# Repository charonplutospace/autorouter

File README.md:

# autorouter
A test for an reinforement based autorouter
A test for an reinforement based autorouter

The readme describtion continues.

pip install -r requirements.txt
PyQt6

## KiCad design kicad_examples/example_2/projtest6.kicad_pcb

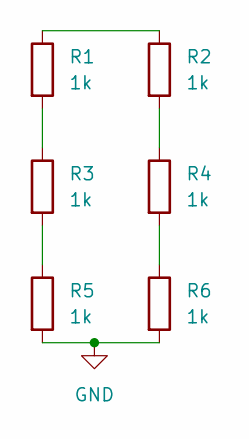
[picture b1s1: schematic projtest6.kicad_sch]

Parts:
R1, R2, R3, R4, R5, R6: 1k; R_1206_3216Metric

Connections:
GND: R5.2, R6.2
unnamed: R1.1, R2.1
unnamed: R1.2, R3.1
unnamed: R2.2, R4.1
unnamed: R3.2, R5.1
unnamed: R4.2, R6.1

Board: 2 copper layers, 6 parts (0 on the bottom side), 6 nets, no tracks yet.

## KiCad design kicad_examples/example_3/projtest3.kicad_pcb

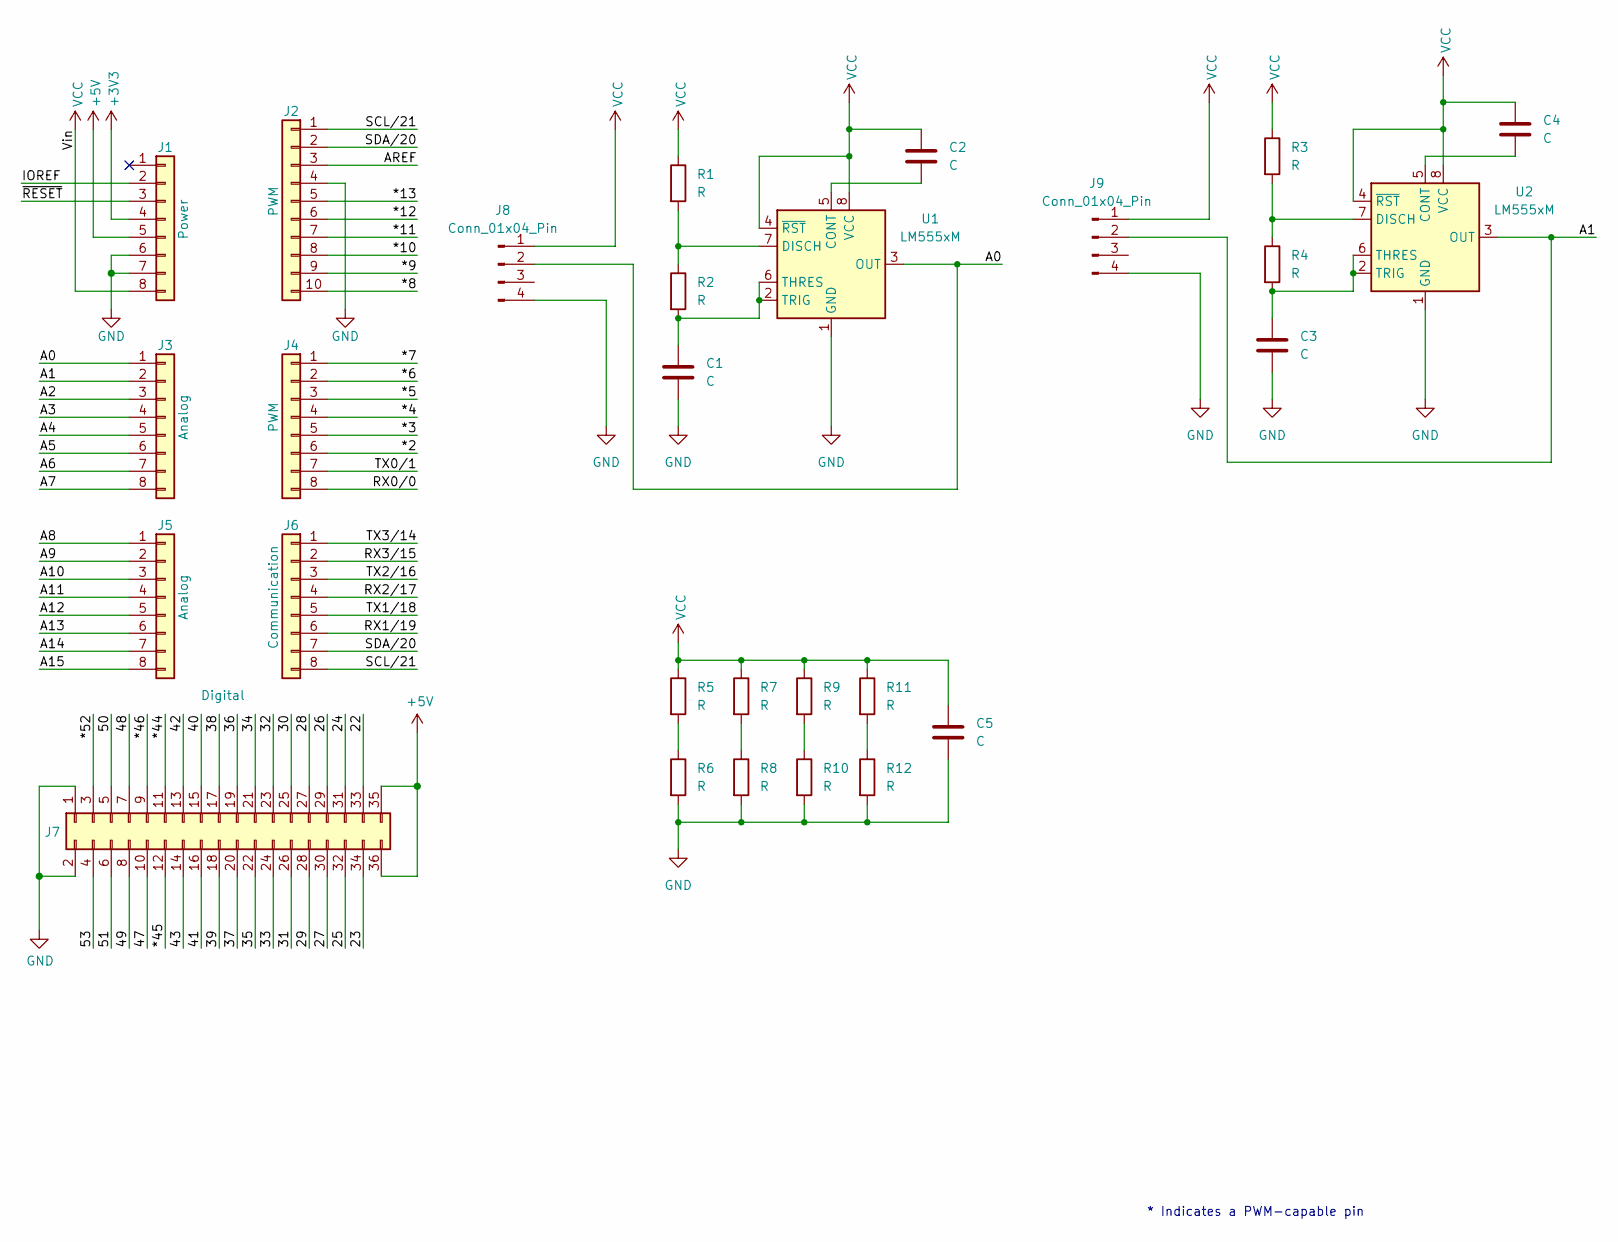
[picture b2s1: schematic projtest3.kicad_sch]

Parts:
C1, C3, C5: C; C_1812_4532Metric
C2, C4: C; C_1206_3216Metric
J1: Power; PinSocket_1x08_P2.54mm_Vertical
J2: PWM; PinSocket_1x10_P2.54mm_Vertical
J3, J5: Analog; PinSocket_1x08_P2.54mm_Vertical
J4: PWM; PinSocket_1x08_P2.54mm_Vertical
J6: Communication; PinSocket_1x08_P2.54mm_Vertical
J7: Digital; PinSocket_2x18_P2.54mm_Vertical
J8, J9: Conn_01x04_Pin; JST_EH_B4B-EH-A_1x04_P2.50mm_Vertical
R1, R2, R3, R4: R; R_1206_3216Metric
R5, R6, R7, R8, R9, R10, R11, R12: R; R_Axial_DIN0204_L3.6mm_D1.6mm_P7.62mm_Horizontal
U1, U2: LM555xM; SOIC-8_3.9x4.9mm_P1.27mm

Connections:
+3V3: J1.4
+5V: J1.5, J7.35, J7.36
/22: J7.33
/23: J7.34
/24: J7.31
/25: J7.32
/26: J7.29
/27: J7.30
/28: J7.27
/29: J7.28
/30: J7.25
/31: J7.26
/32: J7.23
/33: J7.24
/34: J7.21
/35: J7.22
/36: J7.19
/37: J7.20
/38: J7.17
/39: J7.18
/40: J7.15
/41: J7.16
/42: J7.13
/43: J7.14
/47: J7.10
/48: J7.7
/49: J7.8
/50: J7.5
/51: J7.6
/53: J7.4
/*2: J4.6
/*3: J4.5
/*4: J4.4
/*5: J4.3
/*6: J4.2
/*7: J4.1
/*8: J2.10
/*9: J2.9
/*10: J2.8
/*11: J2.7
/*12: J2.6
/*13: J2.5
/*44: J7.11
/*45: J7.12
/*46: J7.9
/*52: J7.3
/A0: J3.1, J8.2, U1.3 (OUT)
/A1: J3.2, J9.2, U2.3 (OUT)
/A2: J3.3
/A3: J3.4
/A4: J3.5
/A5: J3.6
/A6: J3.7
/A7: J3.8
/A8: J5.1
/A9: J5.2
/A10: J5.3
/A11: J5.4
/A12: J5.5
/A13: J5.6
/A14: J5.7
/A15: J5.8
/AREF: J2.3
/IOREF: J1.2
/RX0/0: J4.8
/RX1/19: J6.6
/RX2/17: J6.4
/RX3/15: J6.2
/SCL/21: J2.1, J6.8
/SDA/20: J2.2, J6.7
/TX0/1: J4.7
/TX1/18: J6.5
/TX2/16: J6.3
/TX3/14: J6.1
/~RESET: J1.3
GND: C1.2, C3.2, C5.2, J1.6, J1.7, J2.4, J7.1, J7.2, J8.4, J9.4, R6.2, R8.2, R10.2, R12.2, U1.1 (GND), U2.1 (GND)
unnamed: R5.2, R6.1
unnamed: R7.2, R8.1
unnamed: R9.2, R10.1
unnamed: R11.2, R12.1
unnamed: C2.2, U1.5 (CONT)
unnamed: R1.2, R2.1, U1.7 (DISCH)
unnamed: C1.1, R2.2, U1.2 (TRIG), U1.6 (THRES)
unnamed: C4.2, U2.5 (CONT)
unnamed: R3.2, R4.1, U2.7 (DISCH)
unnamed: C3.1, R4.2, U2.2 (TRIG), U2.6 (THRES)
VCC: C2.1, C4.1, C5.1, J1.8, J8.1, J9.1, R1.1, R3.1, R5.1, R7.1, R9.1, R11.1, U1.4 (~RST), U1.8 (VCC), U2.4 (~RST), U2.8 (VCC)

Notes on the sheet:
* Indicates a PWM-capable pin

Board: 2 copper layers, 34 parts (0 on the bottom side), 17 nets, no tracks yet.

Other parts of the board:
MH1, MH2, MH3, MH4, MH5, MH6: MountingHole_3.2mm

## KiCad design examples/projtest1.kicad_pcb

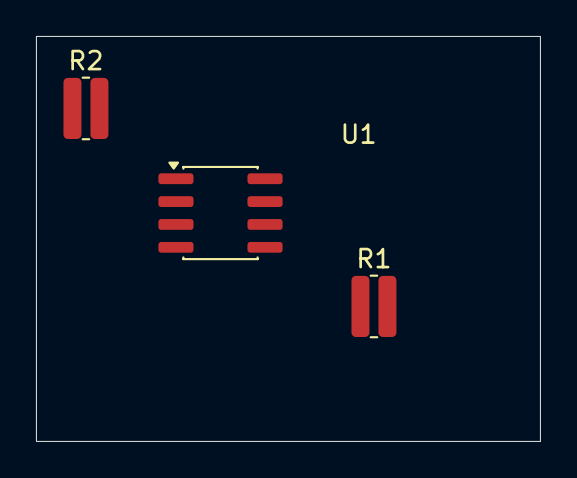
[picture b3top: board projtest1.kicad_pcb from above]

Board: 2 copper layers, 28.0 x 22.5 mm, 3 parts (0 on the bottom side), 4 nets, no tracks yet.

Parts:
R1, R2: R; R_0612_1632Metric
U1: LM555xM; SOIC-8_3.9x4.9mm_P1.27mm

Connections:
unnamed: R1.2, U1.7 (DISCH)
unnamed: R2.2, U1.1 (GND), U1.2 (TRIG)
unnamed: R2.1, U1.3 (OUT)
unnamed: R1.1, U1.4 (~RST)

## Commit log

2026-06-26 Update README with additional description
    Added additional description to README.
2026-06-26 update
    This commit adds a new KiCad project file with various design settings, rules, and configurations for a PCB layout.
